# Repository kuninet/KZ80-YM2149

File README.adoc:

== KZ80シリーズ用 PSG音源(YM2149/AY-3-8910)ボード

=== 概要
* SBC8080バスにつながるPSG音源(YM2149/AY-3-8910)ボードのプロジェクトです。
* 詳しい説明は以下のwikiをご覧ください。
** https://github.com/kuninet/KZ80-YM2149/wiki

image::image/KZ80-YM2149.jpg[]

=== ライセンス
* 本プロジェクトのデータはMITライセンスのもとで公開します。

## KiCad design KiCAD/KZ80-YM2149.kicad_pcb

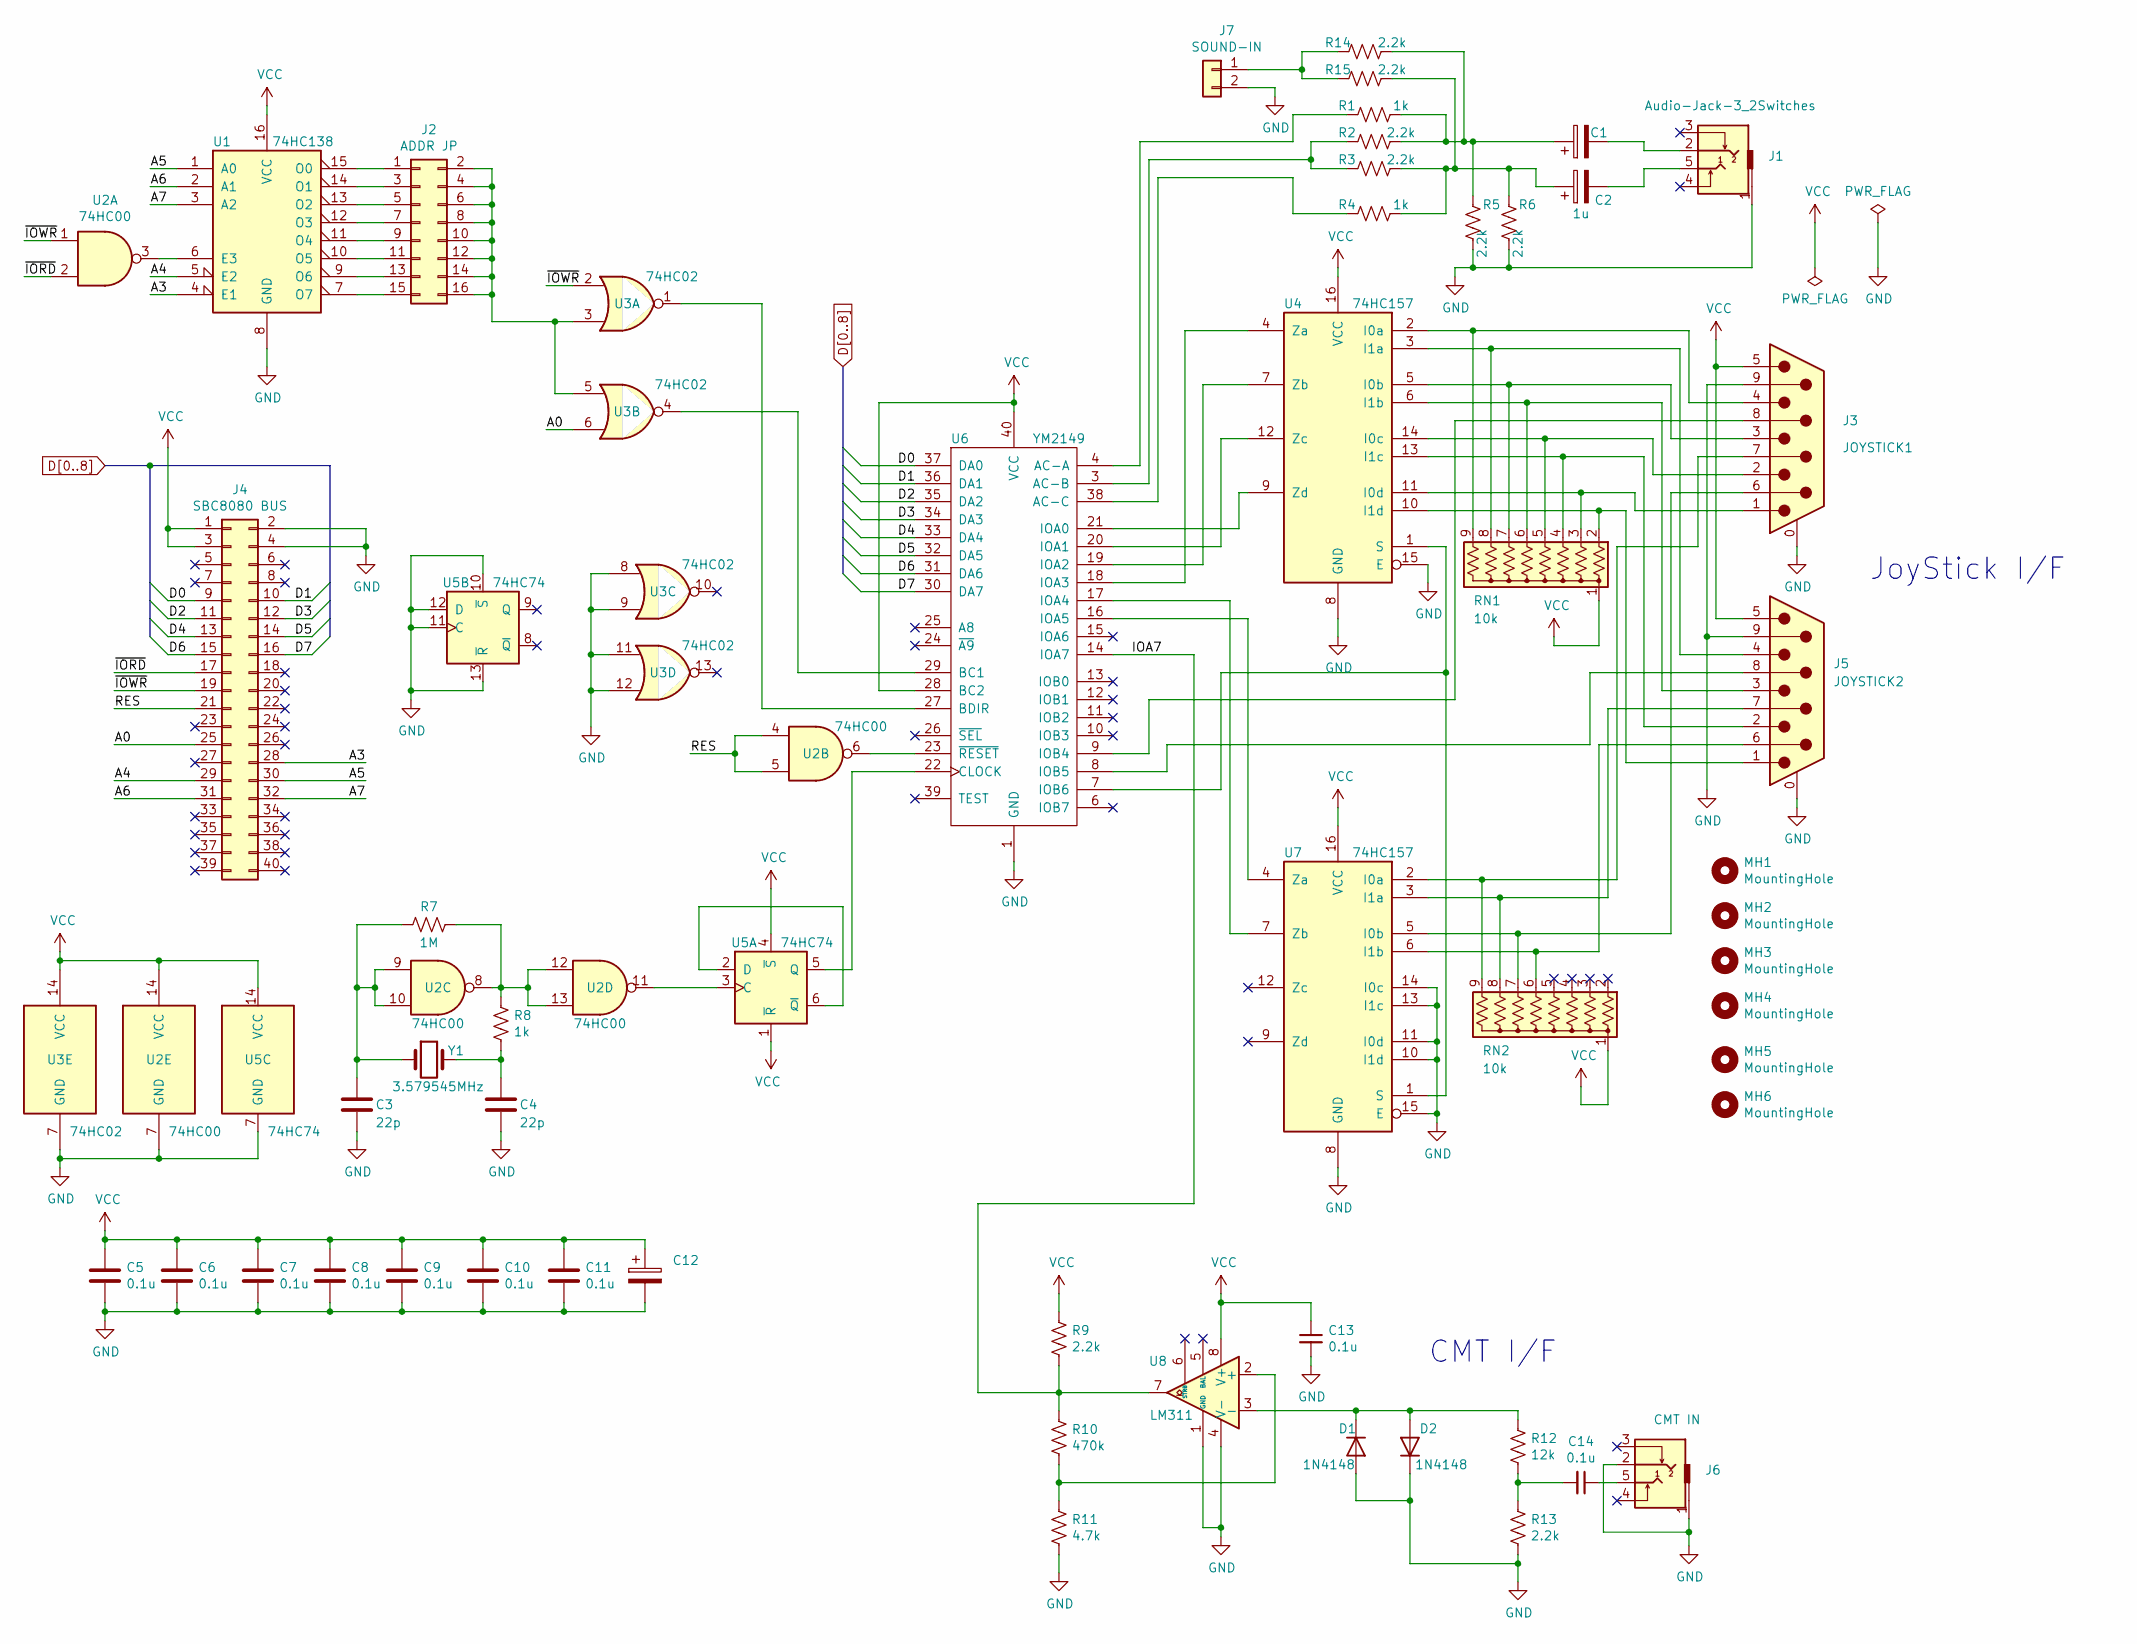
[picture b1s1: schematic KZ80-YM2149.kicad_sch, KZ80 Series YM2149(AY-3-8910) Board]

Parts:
C1, C12: (no value)
C2: 1u
C3, C4: 22p; C_Disc_D3.0mm_W1.6mm_P2.50mm
C5, C6, C7, C8, C9, C10, C11, C13, C14: 0.1u; C_Disc_D3.0mm_W1.6mm_P2.50mm
D1, D2: 1N4148; D_DO-35_SOD27_P7.62mm_Horizontal
J1: Audio-Jack-3_2Switches; AJ-1780
J2: ADDR JP; PinHeader_2x08_P2.54mm_Vertical
J3: JOYSTICK1; DSUB-9_Male_Horizontal_P2.77x2.54mm_EdgePinOffset9.40mm
J4: SBC8080 BUS; PinHeader_2x20_P2.54mm_Horizontal
J5: JOYSTICK2; DSUB-9_Male_Horizontal_P2.77x2.54mm_EdgePinOffset9.40mm
J6: CMT IN; AJ-1780
J7: SOUND-IN; PinHeader_1x02_P2.54mm_Vertical
MH1, MH2, MH3, MH4, MH5, MH6: MountingHole; MountingHole_3.2mm_M3
R1, R4, R8: 1k; R_Axial_DIN0207_L6.3mm_D2.5mm_P10.16mm_Horizontal
R2, R3, R5, R6, R9, R13, R14, R15: 2.2k; R_Axial_DIN0207_L6.3mm_D2.5mm_P10.16mm_Horizontal
R7: 1M; R_Axial_DIN0207_L6.3mm_D2.5mm_P10.16mm_Horizontal
R10: 470k; R_Axial_DIN0207_L6.3mm_D2.5mm_P10.16mm_Horizontal
R11: 4.7k; R_Axial_DIN0207_L6.3mm_D2.5mm_P10.16mm_Horizontal
R12: 12k; R_Axial_DIN0207_L6.3mm_D2.5mm_P10.16mm_Horizontal
RN1, RN2: 10k; R_Array_SIP9
U1: 74HC138; DIP-16_W7.62mm_Socket
U2: 74HC00; DIP-14_W7.62mm_Socket
U3: 74HC02; DIP-14_W7.62mm_Socket
U4, U7: 74HC157; DIP-16_W7.62mm_Socket
U5: 74HC74; DIP-14_W7.62mm_Socket
U6: YM2149; DIP-40_W15.24mm_Socket
U8: LM311; DIP-8_W7.62mm_Socket_LongPads
Y1: 3.579545MHz; Crystal_HC49-U_Vertical

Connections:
/A0: J4.25, U3.6
/A3: J4.28, U1.4 (E1)
/A4: J4.29, U1.5 (E2)
/A5: J4.30, U1.1 (A0)
/A6: J4.31, U1.2 (A1)
/A7: J4.32, U1.3 (A2)
/IOA7: R9.2, R10.1, U6.14 (IOA7), U8.7
/RES: J4.21, U2.4, U2.5
/~IORD: J4.17, U2.2
/~IOWR: J4.19, U2.1, U3.2
D0: J4.9, U6.37 (DA0)
D1: J4.10, U6.36 (DA1)
D2: J4.11, U6.35 (DA2)
D3: J4.12, U6.34 (DA3)
D4: J4.13, U6.33 (DA4)
D5: J4.14, U6.32 (DA5)
D6: J4.15, U6.31 (DA6)
D7: J4.16, U6.30 (DA7)
GND: C3.2, C4.2, C5.2, C6.2, C7.2, C8.2, C9.2, C10.2, C11.2, C12.2, C13.2, D1.2 (A), D2.1 (K), J1.1, J3.0 (PAD), J3.9, J4.2, J4.4, J5.0 (PAD), J5.9, J6.1, J6.2, J7.2, R5.2, R6.2, R11.2, R13.2, U1.8 (GND), U2.7 (GND), U3.7 (GND), U3.8, U3.9, U3.11, U3.12, U4.8 (GND), U4.15 (E), U5.7 (GND), U5.10 (~S), U5.11 (C), U5.12 (D), U5.13 (~R), U6.1 (GND), U7.8 (GND), U7.10 (I1d), U7.11 (I0d), U7.13 (I1c), U7.14 (I0c), U7.15 (E), U8.1 (GND), U8.4 (V-)
unnamed: C3.1, R7.2, U2.9, U2.10, Y1.1
unnamed: C4.1, R8.2, Y1.2
unnamed: C14.1, J6.5
unnamed: C14.2, R12.2, R13.1
unnamed: D1.1 (K), D2.2 (A), R12.1, U8.3 (-)
unnamed: C1.2, J1.2
unnamed: C2.2, J1.5
unnamed: J2.1, U1.15 (O0)
unnamed: J2.3, U1.14 (O1)
unnamed: J2.5, U1.13 (O2)
unnamed: J2.7, U1.12 (O3)
unnamed: J2.9, U1.11 (O4)
unnamed: J2.2, J2.4, J2.6, J2.8, J2.10, J2.12, J2.14, J2.16, U3.3, U3.5
unnamed: J2.11, U1.10 (O5)
unnamed: J2.13, U1.9 (O6)
unnamed: J2.15, U1.7 (O7)
unnamed: J3.1, RN1.3 (R2), U4.11 (I0d)
unnamed: J3.2, RN1.5 (R4), U4.14 (I0c)
unnamed: J3.3, RN1.7 (R6), U4.5 (I0b)
unnamed: J3.4, RN1.9 (R8), U4.2 (I0a)
unnamed: J3.6, RN2.7 (R6), U7.5 (I0b)
unnamed: J3.7, RN2.9 (R8), U7.2 (I0a)
unnamed: J3.8, U6.9 (IOB4)
unnamed: J5.1, RN1.2 (R1), U4.10 (I1d)
unnamed: J5.2, RN1.4 (R3), U4.13 (I1c)
unnamed: J5.3, RN1.6 (R5), U4.6 (I1b)
unnamed: J5.4, RN1.8 (R7), U4.3 (I1a)
unnamed: J5.6, RN2.6 (R5), U7.6 (I1b)
unnamed: J5.7, RN2.8 (R7), U7.3 (I1a)
unnamed: J5.8, U6.8 (IOB5)
unnamed: J7.1, R14.2, R15.2
unnamed: C1.1, R1.1, R2.1, R5.1, R14.1
unnamed: R1.2, U6.4 (AC-A)
unnamed: R2.2, R3.2, U6.3 (AC-B)
unnamed: R4.2, U6.38 (AC-C)
unnamed: R7.1, R8.1, U2.8, U2.12, U2.13
unnamed: R10.2, R11.1, U8.2 (+)
unnamed: C2.1, R3.1, R4.1, R6.1, R15.1
unnamed: U1.6 (E3), U2.3
unnamed: U2.6, U6.23 (~RESET)
unnamed: U2.11, U5.3 (C)
unnamed: U3.1, U6.27 (BDIR)
unnamed: U3.4, U6.29 (BC1)
unnamed: U4.1 (S), U6.7 (IOB6), U7.1 (S)
unnamed: U4.4 (Za), U6.18 (IOA3)
unnamed: U4.7 (Zb), U6.19 (IOA2)
unnamed: U4.9 (Zd), U6.21 (IOA0)
unnamed: U4.12 (Zc), U6.20 (IOA1)
unnamed: U5.2 (D), U5.6 (~Q)
unnamed: U5.5 (Q), U6.22 (CLOCK)
unnamed: U6.16 (IOA5), U7.4 (Za)
unnamed: U6.17 (IOA4), U7.7 (Zb)
VCC: C5.1, C6.1, C7.1, C8.1, C9.1, C10.1, C11.1, C12.1, C13.1, J3.5, J4.1, J4.3, J5.5, R9.1, RN1.1 (common), RN2.1 (common), U1.16 (VCC), U2.14 (VCC), U3.14 (VCC), U4.16 (VCC), U5.1 (~R), U5.4 (~S), U5.14 (VCC), U6.28 (BC2), U6.40 (VCC), U7.16 (VCC), U8.8 (V+)

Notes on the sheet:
JoyStick I/F
CMT I/F

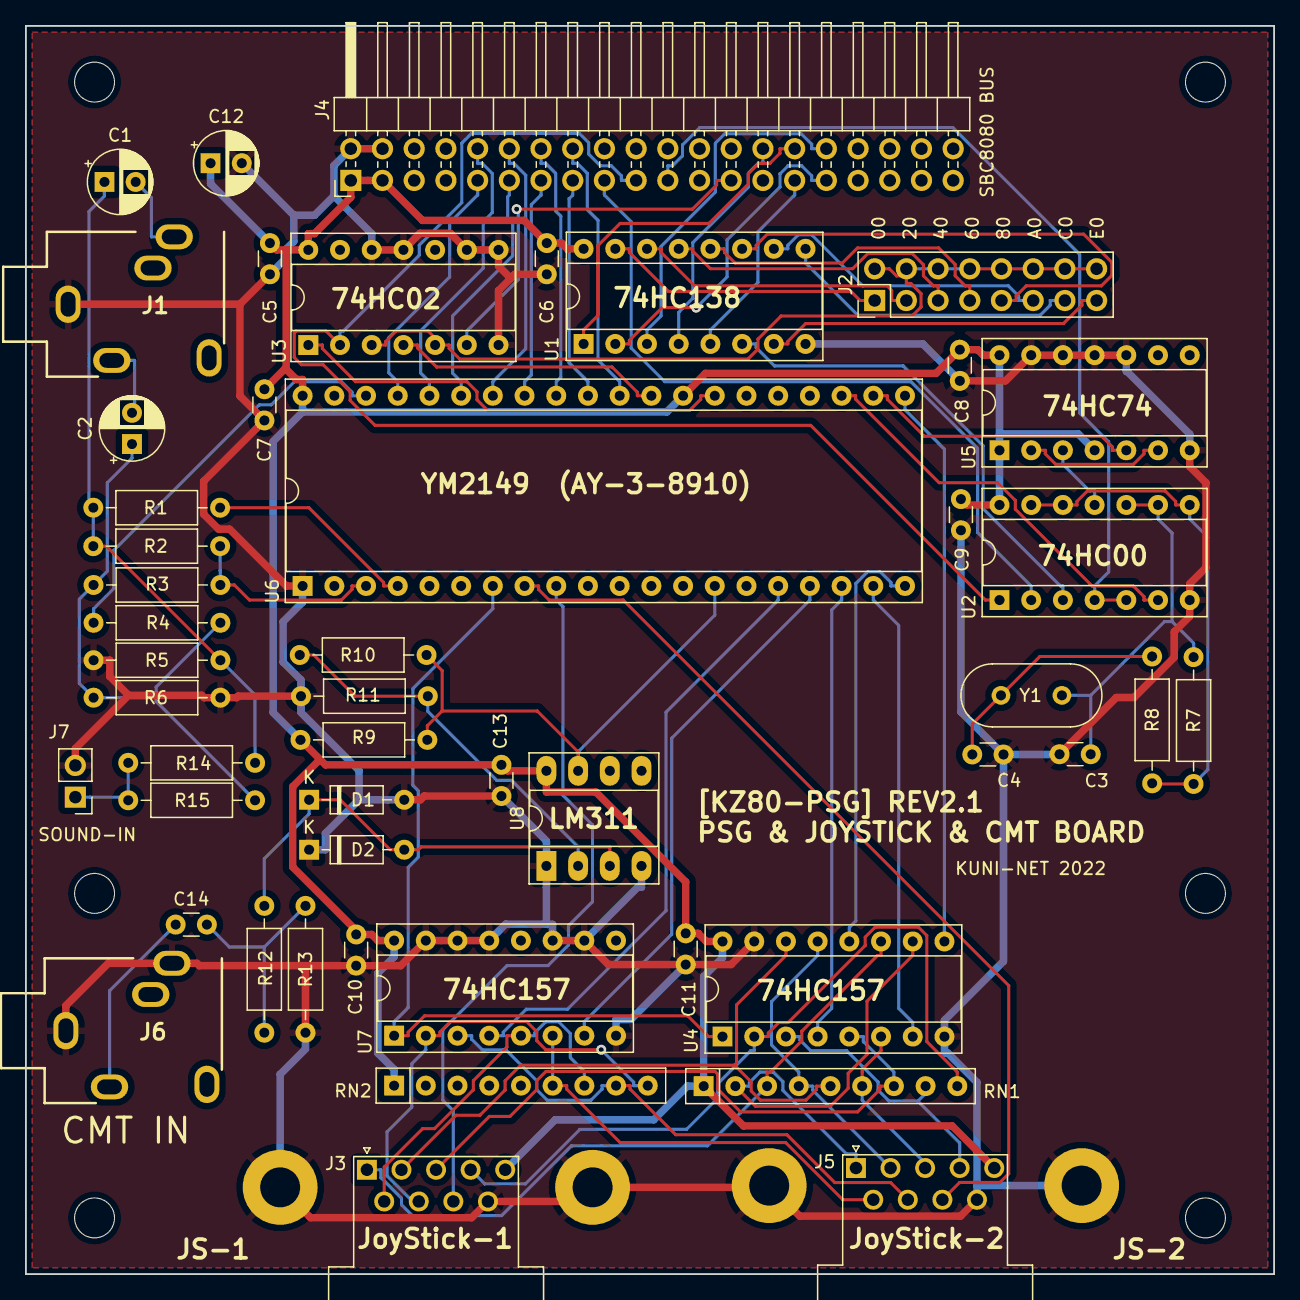
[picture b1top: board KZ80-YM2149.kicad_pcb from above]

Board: 2 copper layers, 100.0 x 100.0 mm, 55 parts (0 on the bottom side), 72 nets.

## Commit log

2019-07-16 init commit
2019-07-16 Create LICENSE
2019-07-16 README更新 & 回路図イメージ添付
2019-08-10 ジョイスティックポート接続&プリントパターン見直し
2019-08-10 パターン間違い修正&ガーバーデータ再出力
2019-08-11 演奏プログラムサンプル追加
2019-08-11 演奏プログラム 曲データアドレス変更→$9000
2019-08-17 ジョイスティックテストCプログラム作成
2019-09-02 回路図 クロック等 微修正
2019-09-07 ガーバーデータ出力項目見直し。ガーバーデータ再出力
2019-09-07 ガーバーデータ出力項目見直し分、追加コミット
2019-09-07 ジョイスティック シルク追加
2021-03-22 REV2基板 回路回路、パターン作成・ガーバー出力
2021-03-22 REV1回路図分離
2021-03-22 回路図間違い修正・ガーバー再出力
2021-03-22 回路図差し替え
2022-06-07 KiCAD6対応 & CMTステレオジャック回路修正 ・ガーバー2.1出力 #2
2022-06-07 コンデンサシンボル変更忘れ対応 #2
2022-06-07 回路図イメージ差し替え
2022-11-01 REV2.1ガーバーデータ再作成
